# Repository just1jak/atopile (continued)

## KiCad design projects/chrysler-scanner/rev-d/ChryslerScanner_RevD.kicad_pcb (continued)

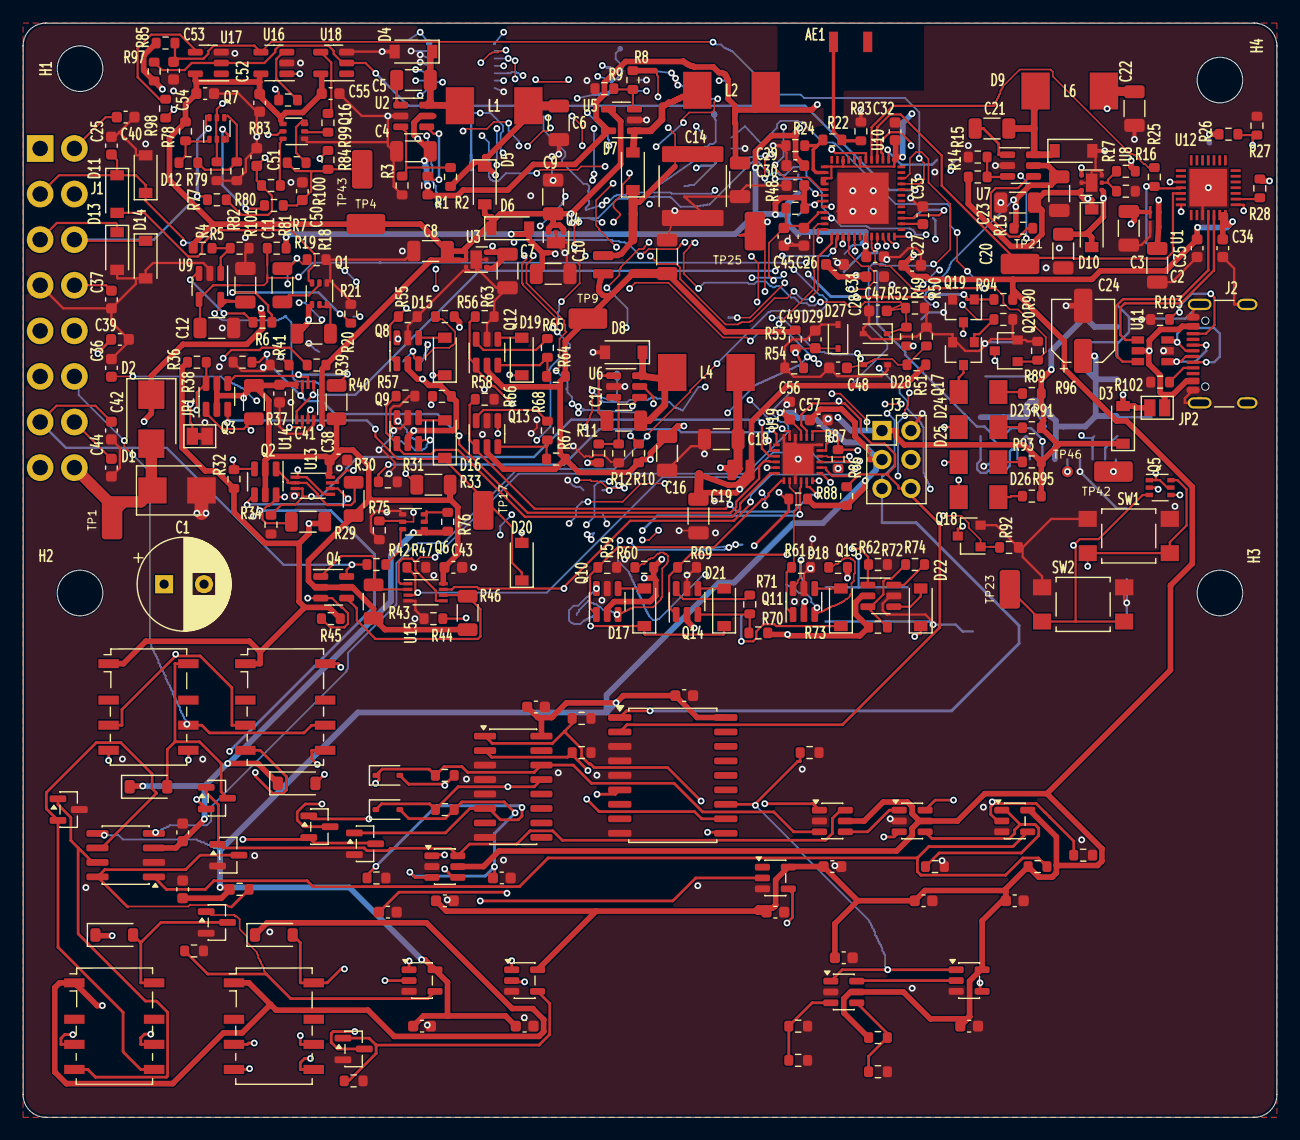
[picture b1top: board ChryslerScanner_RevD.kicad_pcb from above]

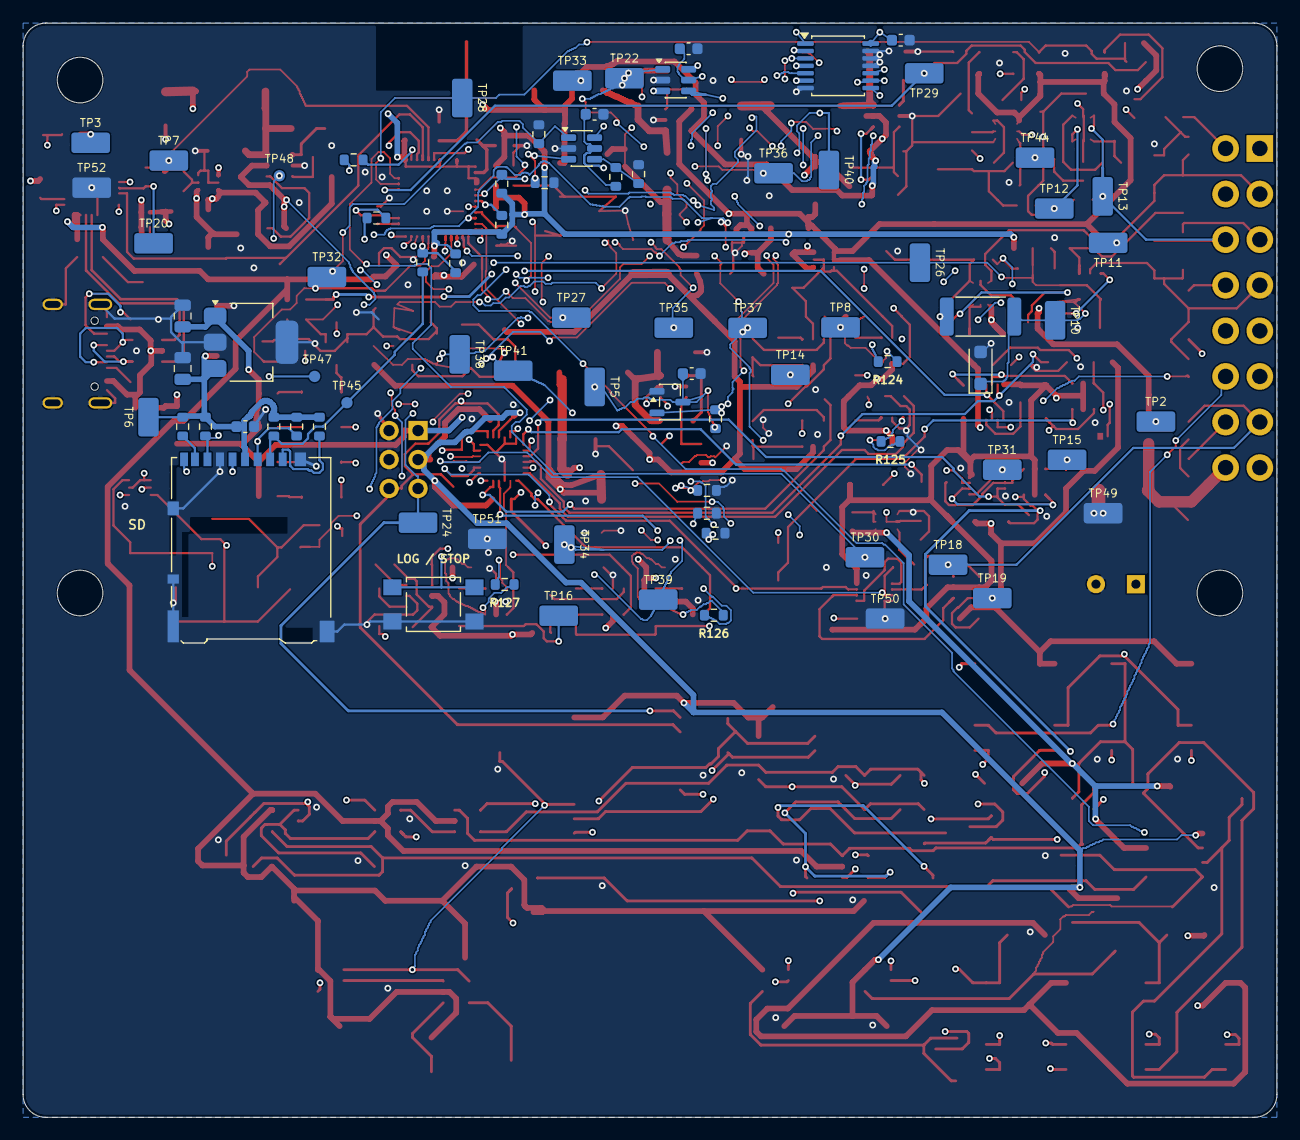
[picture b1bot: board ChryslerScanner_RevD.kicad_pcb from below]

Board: 4 copper layers, 110.0 x 96.0 mm, 397 parts (81 on the bottom side), 201 nets.

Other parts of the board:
C62, C63, C64, C65: 100nF 16V X7R; C_0603_1608Metric
D30: BZT52H-B15; D_SOD-123F
H1, H2, H3, H4: MountingHole_4mm
R115: 100k 0.1% 25ppm; R_0603_1608Metric
R116: 191k 1%; R_0603_1608Metric
R117, R120, R121, R122: 100k 1%; R_0603_1608Metric
R118, R119: 10k 1%; R_0603_1608Metric
R123: 1k 1W 1%; R_2512_6332Metric
U21: TMUX1511PWR; TSSOP-14_4.4x5mm_P0.65mm
U22: LTC6993HS6-2#TRMPBF; TSOT-23-6
U23: SN74LVC1G11DBVR; SOT-23-6
U24: TLV803EA30DBZR; SOT-23-3

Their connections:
+3.3V: C62.1, C63.1, C64.1, C65.1, R116.1, R119.1, U21.14, U22.5, U23.5, U24.3; also elsewhere on the board
+12V: R123.1; also elsewhere on the board
ACT_LED: R118.1, U22.1; also elsewhere on the board
EN: U23.1; also elsewhere on the board
GND: C62.2, C63.2, C64.2, C65.2, D30.2, R115.2, R117.2, R118.2, R120.2, R121.2, R122.2, U21.7, U21.11, U21.12, U21.13, U22.2, U23.2, U24.1; also elsewhere on the board
HEARTBEAT_VALID: U22.6, U23.6; also elsewhere on the board
LOGIC_PG: R119.2, U21.1, U21.4, U21.10, U23.3, U24.2; also elsewhere on the board
N_R88_2: U23.4; also elsewhere on the board
PCI_VCC: D30.1, R123.2; also elsewhere on the board
V_BA: R120.1, U21.3; also elsewhere on the board
V_BA_PRE: U21.2; also elsewhere on the board
V_BT: R121.1, U21.6; also elsewhere on the board
V_BT_PRE: U21.5; also elsewhere on the board
V_PR: R122.1, U21.8; also elsewhere on the board
V_PR_PRE: U21.9; also elsewhere on the board
WD_DIV: R116.2, R117.1, U22.4
WD_SET: R115.1, U22.3

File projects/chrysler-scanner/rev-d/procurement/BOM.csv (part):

"Reference","Value","Footprint","Manufacturer","MPN","LCSC Part #","Assembly","Source"
"AE1","ANT3216LL00R2400A","footprints:ANT3216LL00R2400A","Walsin","ANT3216LL00R2400A","C293767","PLACE","https://www.passivecomponent.com/antenna/"
"C1","100μF","footprints:CP_Radial_D8.0mm_P3.50mm","Nichicon","UPW1H101MPD","C125987","PLACE","https://www.nichicon.co.jp/english/series_items/catalog_pdf/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"
"C2","10μF","footprints:C_1206_3216Metric","TDK","CGA5L1X7R1H106K160AC","","PLACE","https://product.tdk.com/info/en/documents/chara_sheet/CGA5L1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"
"C3","10μF","footprints:C_1206_3216Metric","TDK","CGA5L1X7R1H106K160AC","","PLACE","https://product.tdk.com/info/en/documents/chara_sheet/CGA5L1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"
"C4","10μF","footprints:C_1206_3216Metric","TDK","CGA5L1X7R1H106K160AC","","PLACE","https://product.tdk.com/info/en/documents/chara_sheet/CGA5L1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"
"C5","0.1μF","footprints:C_1206_3216Metric","KEMET","C1206C104K1RACTU","C2167118","PLACE","https://search.kemet.com/component-documentation/download/sp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"
"C6","22μF","footprints:C_1206_3216Metric","TDK","C3216X5R1E226M160AB","","PLACE","https://product.tdk.com/en/search/capacitor/ceramic/mlcc/inf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"
"C7","10μF","footprints:C_1206_3216Metric","TDK","CGA5L1X7R1H106K160AC","","PLACE","https://product.tdk.com/info/en/documents/chara_sheet/CGA5L1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"
"C8","22μF","footprints:C_1206_3216Metric","TDK","C3216X5R1E226M160AB","","PLACE","https://product.tdk.com/en/search/capacitor/ceramic/mlcc/inf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"
"C9","10μF","footprints:C_1206_3216Metric","TDK","CGA5L1X7R1H106K160AC","","PLACE","https://product.tdk.com/info/en/documents/chara_sheet/CGA5L1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"
"C10","22μF","footprints:C_1206_3216Metric","TDK","C3216X5R1E226M160AB","","PLACE","https://product.tdk.com/en/search/capacitor/ceramic/mlcc/inf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"
"C11","0.1μF","footprints:C_1206_3216Metric","KEMET","C1206C104K1RACTU","C2167118","PLACE","https://search.kemet.com/component-documentation/download/sp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"
"C12","220pF","footprints:C_1206_3216Metric","KEMET","C1206C221J1GACTU","","PLACE","https://search.kemet.com/component-documentation/download/sp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"
"C13","10μF","footprints:C_1206_3216Metric","TDK","CGA5L1X7R1H106K160AC","","PLACE","https://product.tdk.com/info/en/documents/chara_sheet/CGA5L1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"
"C14","22μF","footprints:C_2220_5750_TDK_22u50V","TDK","CGA9P3X7R1H226MT0Y0N","C49297044","PLACE","https://jlcpcb.com/partdetail/TDK-CGA9P3X7R1H226MT0Y0N/C49297044"
"C15","10μF","footprints:C_1206_3216Metric","TDK","CGA5L1X7R1H106K160AC","","PLACE","https://product.tdk.com/info/en/documents/chara_sheet/CGA5L1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"
"C16","10μF","footprints:C_1206_3216Metric","TDK","CGA5L1X7R1H106K160AC","","PLACE","https://product.tdk.com/info/en/documents/chara_sheet/CGA5L1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"
"C17","0.1μF","footprints:C_1206_3216Metric","KEMET","C1206C104K1RACTU","C2167118","PLACE","https://search.kemet.com/component-documentation/download/sp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"
"C18","22μF","footprints:C_1206_3216Metric","TDK","C3216X5R1E226M160AB","","PLACE","https://product.tdk.com/en/search/capacitor/ceramic/mlcc/inf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"
"C19","10μF","footprints:C_1206_3216Metric","TDK","CGA5L1X7R1H106K160AC","","PLACE","https://product.tdk.com/info/en/documents/chara_sheet/CGA5L1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"
"C20","10μF","footprints:C_1206_3216Metric","TDK","CGA5L1X7R1H106K160AC","","PLACE","https://product.tdk.com/info/en/documents/chara_sheet/CGA5L1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"
"C21","0.1μF","footprints:C_1206_3216Metric","KEMET","C1206C104K1RACTU","C2167118","PLACE","https://search.kemet.com/component-documentation/download/sp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"
"C22","22μF","footprints:C_1206_3216Metric","TDK","C3216X5R1E226M160AB","","PLACE","https://product.tdk.com/en/search/capacitor/ceramic/mlcc/inf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"
"C23","10μF","footprints:C_1206_3216Metric","TDK","CGA5L1X7R1H106K160AC","","PLACE","https://product.tdk.com/info/en/documents/chara_sheet/CGA5L1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"
"C24","22μF","footprints:C_1206_3216Metric","TDK","C3216X5R1E226M160AB","","PLACE","https://product.tdk.com/en/search/capacitor/ceramic/mlcc/inf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"
"C25","220pF","footprints:C_0603_1608Metric","KEMET","C0603C221J1GACTU","","PLACE","https://search.kemet.com/component-documentation/download/sp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"
"C26","10μF","footprints:C_0603_1608Metric","TDK","C1608X5R1A106K080AC","","PLACE","https://product.tdk.com/en/search/capacitor/ceramic/mlcc/inf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"
"C27","10μF","footprints:C_0603_1608Metric","TDK","C1608X5R1A106K080AC","","PLACE","https://product.tdk.com/en/search/capacitor/ceramic/mlcc/inf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"
"C28","10μF","footprints:C_0603_1608Metric","TDK","C1608X5R1A106K080AC","","PLACE","https://product.tdk.com/en/search/capacitor/ceramic/mlcc/inf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"
"C29","0.1μF","footprints:C_0603_1608Metric","KEMET","C0603C104K5RACTU","C127833","PLACE","https://search.kemet.com/component-documentation/download/sp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"
"C30","0.1μF","footprints:C_0603_1608Metric","KEMET","C0603C104K5RACTU","C127833","PLACE","https://search.kemet.com/component-documentation/download/sp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"
"C31","0.1μF","footprints:C_0603_1608Metric","KEMET","C0603C104K5RACTU","C127833","PLACE","https://search.kemet.com/component-documentation/download/sp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"
"C32","0.1μF","footprints:C_0603_1608Metric","KEMET","C0603C104K5RACTU","C127833","PLACE","https://search.kemet.com/component-documentation/download/sp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"
"C33","0.1μF","footprints:C_0603_1608Metric","KEMET","C0603C104K5RACTU","C127833","PLACE","https://search.kemet.com/component-documentation/download/sp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"
"C34","0.1μF","footprints:C_0603_1608Metric","KEMET","C0603C104K5RACTU","C127833","PLACE","https://search.kemet.com/component-documentation/download/sp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"
"C35","10μF","footprints:C_0603_1608Metric","TDK","C1608X5R1A106K080AC","","PLACE","https://product.tdk.com/en/search/capacitor/ceramic/mlcc/inf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"
"C36","220pF","footprints:C_0603_1608Metric","KEMET","C0603C221J1GACTU","","PLACE","https://search.kemet.com/component-documentation/download/sp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"
"C37","220pF","footprints:C_0603_1608Metric","KEMET","C0603C221J1GACTU","","PLACE","https://search.kemet.com/component-documentation/download/sp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"
"C38","0.1μF","footprints:C_0603_1608Metric","KEMET","C0603C104K5RACTU","C127833","PLACE","https://search.kemet.com/component-documentation/download/sp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"
"C39","220pF","footprints:C_0603_1608Metric","KEMET","C0603C221J1GACTU","","PLACE","https://search.kemet.com/component-documentation/download/sp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"
"C40","220pF","footprints:C_0603_1608Metric","KEMET","C0603C221J1GACTU","","PLACE","https://search.kemet.com/component-documentation/download/sp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"
"C41","0.1μF","footprints:C_0603_1608Metric","KEMET","C0603C104K5RACTU","C127833","PLACE","https://search.kemet.com/component-documentation/download/sp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"
"C42","220pF","footprints:C_0603_1608Metric","KEMET","C0603C221J1GACTU","","PLACE","https://search.kemet.com/component-documentation/download/sp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"
"C43","0.1μF","footprints:C_0603_1608Metric","KEMET","C0603C104K5RACTU","C127833","PLACE","https://search.kemet.com/component-documentation/download/sp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"
"C44","220pF","footprints:C_0603_1608Metric","KEMET","C0603C221J1GACTU","","PLACE","https://search.kemet.com/component-documentation/download/sp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"
"C45","1μF","footprints:C_0603_1608Metric","KEMET","C0603C105K4RACTU","C2167386","PLACE","https://search.kemet.com/component-documentation/download/sp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"
"C46","0.1μF","footprints:C_0603_1608Metric","KEMET","C0603C104K5RACTU","C127833","PLACE","https://search.kemet.com/component-documentation/download/sp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"
"C47","0.1μF","footprints:C_0603_1608Metric","KEMET","C0603C104K5RACTU","C127833","PLACE","https://search.kemet.com/component-documentation/download/sp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"
"C48","0.1μF","footprints:C_0603_1608Metric","KEMET","C0603C104K5RACTU","C127833","PLACE","https://search.kemet.com/component-documentation/download/sp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"
"C49","0.1μF","footprints:C_0603_1608Metric","KEMET","C0603C104K5RACTU","C127833","PLACE","https://search.kemet.com/component-documentation/download/sp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"
"C50","220pF","footprints:C_0603_1608Metric","KEMET","C0603C221J1GACTU","","PLACE","https://search.kemet.com/component-documentation/download/sp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"
"C51","220pF","footprints:C_0603_1608Metric","KEMET","C0603C221J1GACTU","","PLACE","https://search.kemet.com/component-documentation/download/sp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"
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
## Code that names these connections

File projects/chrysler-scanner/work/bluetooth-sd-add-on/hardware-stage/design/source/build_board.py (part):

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     for zz in ((0,1) if t[2]!=u[2] else (u[2],)):occupied[zz].setdefault((xx,yy),set()).add(net)
 seg((start[0]*STEP,start[1]*STEP),(path[-1][0]*STEP,path[-1][1]*STEP),path[-1][2]);routes.append(dict(net=net,from_=a['ref']+'.'+a['no'],to=b['ref']+'.'+b['no'],steps=len(path)))
# Route pin-local series pairs first, then SPI, power, low-rate controls, ground.
order=['SD_3V3','USB_5V','MCU_3V3','SD_DAT1','SD_DAT2','SD_MISO','SD_CS','SD_MOSI','SD_SCK','MCU_SCK','MCU_MOSI','MCU_CS','LED_GPIO','LED_A','BUTTON']
for net in order:
 ps=[m for m in padmeta if m['net']==net]; connected=[ps.pop(0)]
 while ps:
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
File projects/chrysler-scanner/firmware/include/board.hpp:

// SPDX-License-Identifier: GPL-3.0-only
#pragma once
#include <cstdint>
namespace board {
// ESP32-PICO-V3-02 package-specific mapping; see tools/check_board.py.
constexpr int heartbeat=13, ccd_rx=8, ccd_tx=7, sci_rx=5, sci_tx=4;
constexpr int pci_rx=14, pci_tx=27, usb_rx=3, usb_tx=1, sda=21, scl=22;
constexpr int sd_cs=15, sd_mosi=20, sd_sck=19, sd_miso=36;
constexpr int button=37, card_detect=38;
constexpr unsigned usb_baud=250000;
constexpr std::uint8_t aw_address=0x58;
// AW9523: P0[0:3] VBB, P0[4:7] VPP; P1[0:3] TX selects.
// P1[4] RX7, P1[5] RX15, P1[6] RX7 bias, P1[7] TBEN active LOW.
constexpr std::uint8_t p0_safe=0x00, p1_safe=0x80;
constexpr std::uint8_t rx7=0x10, rx15=0x20;
constexpr char pcb_sha256[]="e794b86979228ba2275eb4262df848acd16e56ef97a4ccf45402d65b119308d4";
}
